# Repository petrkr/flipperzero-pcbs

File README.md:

# Flipper zero PCBs
Repository for expansion board for Flipper Zero

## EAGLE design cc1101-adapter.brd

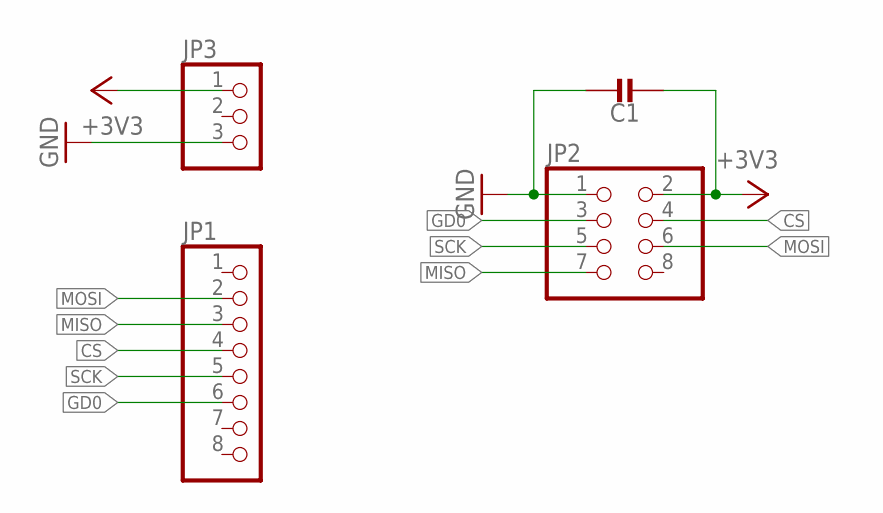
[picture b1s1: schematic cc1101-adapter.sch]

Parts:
C1: CAPACITOR0805_CAP; 0805_CAP
JP1: PINHD-1X8; 1X08
JP2: PINHD-2X4; 2X04
JP3: PINHD-1X3; 1X03

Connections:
+3V3: C1.P$2 (2), JP2.2, JP3.1
CS: JP1.4, JP2.4
GD0: JP1.6, JP2.3
GND: C1.P$1 (1), JP2.1, JP3.3
MISO: JP1.3, JP2.7
MOSI: JP1.2, JP2.6
SCK: JP1.5, JP2.5

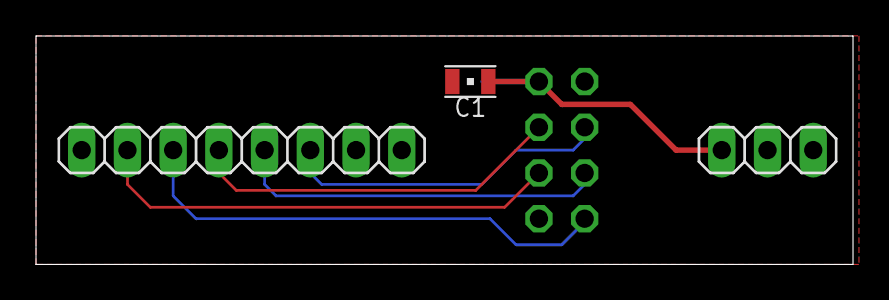
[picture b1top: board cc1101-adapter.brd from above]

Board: 2 copper layers, 45.4 x 12.7 mm, 4 parts (1 on the bottom side), 7 nets.

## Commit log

2023-04-09 Flipper pin header
2023-04-09 CC1101 radio breakout board
2023-04-09 README
2023-04-09 Git ignore
2023-04-09 Create LICENSE
